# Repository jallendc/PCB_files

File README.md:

# PCB_files
PCB files created in EAGLE CAD or other programs

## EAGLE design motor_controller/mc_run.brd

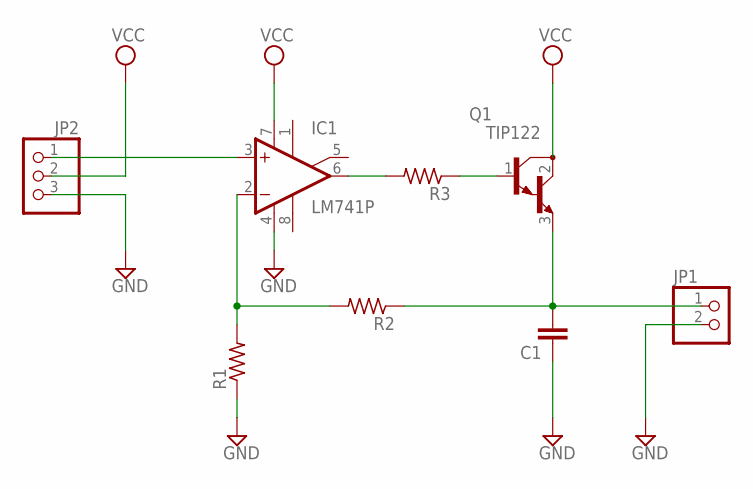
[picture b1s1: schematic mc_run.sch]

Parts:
C1: C7.5/3; C7.5B3
IC1: LM741P; DIL08
JP1: PINHD-1X2; 1X02
JP2: PINHD-1X3; 1X03
Q1: TIP122; TO220
R1, R2, R3: R-US_0411/15; 0411/15

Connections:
GND: C1.1, IC1.4 (V-), JP1.2, JP2.3, R1.1
unnamed: IC1.3 (+IN), JP2.1
unnamed: IC1.6 (OUT), R3.2
unnamed: Q1.1 (B), R3.1
unnamed: C1.2, JP1.1, Q1.3 (E), R2.1
unnamed: IC1.2 (-IN), R1.2, R2.2
VCC: IC1.7 (V+), JP2.2, Q1.2 (C)

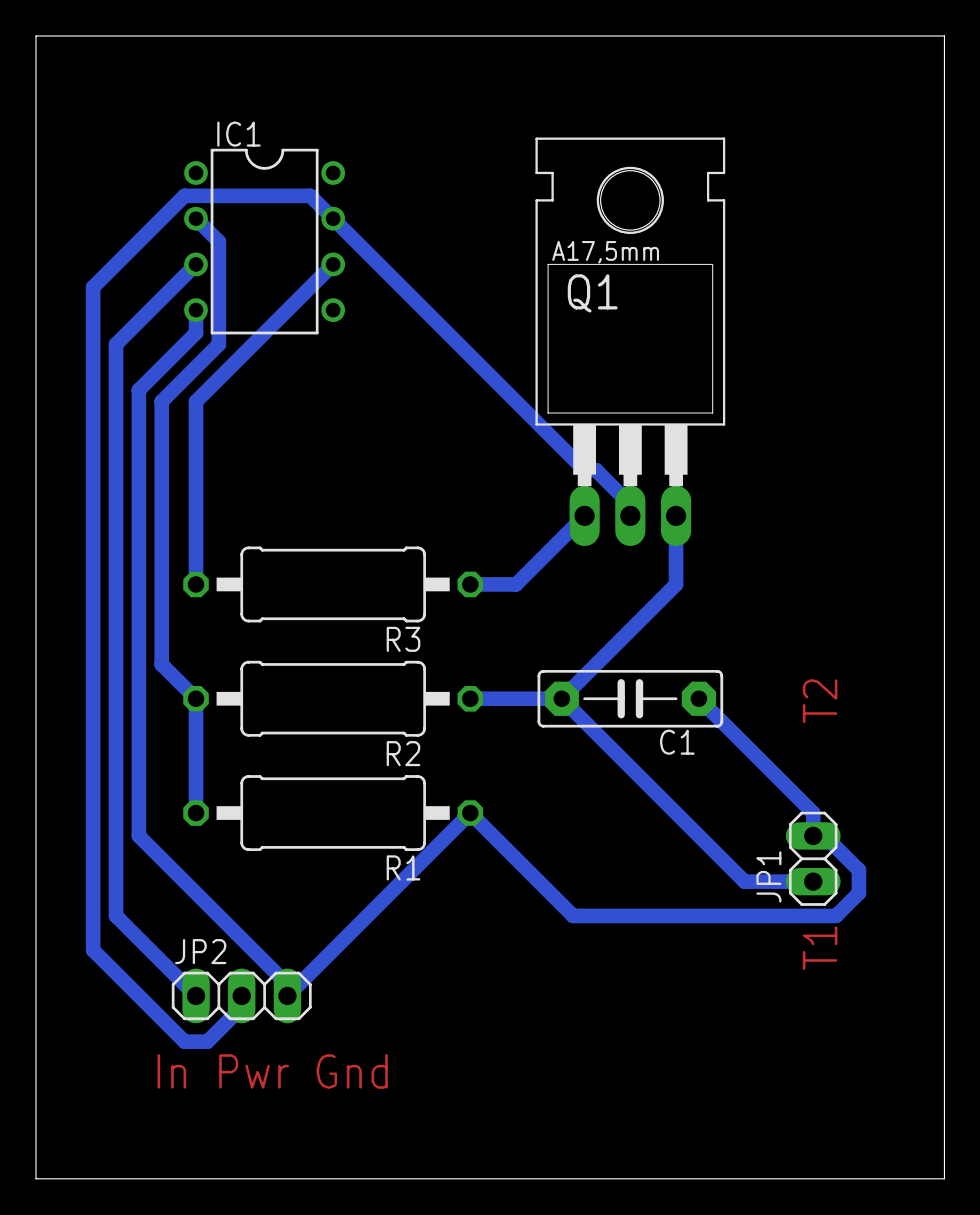
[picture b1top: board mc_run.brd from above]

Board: 2 copper layers, 50.5 x 63.5 mm, 8 parts (0 on the bottom side), 7 nets.

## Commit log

2015-03-05 Total list of all files for motor controller schematic and board design
    Can be opened with Eagle CAD and Gerbv
